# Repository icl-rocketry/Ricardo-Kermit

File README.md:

# Kermit
RAE board designed for data acquisition. All versions currently include power regulation for different types of analog sensors, as well as ADC and TC inputs.

# Supported Versions

## v3
v3 Kermit (nicknamed Kermit mini) includes:
  - [Ricardo Template](https://github.com/icl-rocketry/Ricardo-BoardTemplate) components.
  - 5V and 12V power outputs from an LDO.
  - 4 ADC channels with a theoretical maximum of 64kSPS from 1x ADS131M04 chip. All 4 channels can be configured for differential and single-ended inputs, 4-20mA input, voltage sensor input.
  - 2 Thermocouple chips (MAX31856) supporting every type of thermocouple.
  - SD Card for in-flight, and high rate, data acquisition.
  
## v2
v2 Kermit includes:
  - [Ricardo Template](https://github.com/icl-rocketry/Ricardo-BoardTemplate) components.
  - 5V and 10V power outputs from an LDO.
  - 12 ADC channels with a theoretical maximum of 32kSPS from 2x ADS131M06 chips. All 12 channels can be configured for differential and single-ended inputs, and 3.3V supply voltage sensors. 10 of the channels can be configured for 5v voltage-based sensors, and 2 of the channels can be configured for 4-20mA sensors (10V supply).
  - 4 Thermocouple chips (MAX31856) supporting every type of thermocouple.
  - SD Card for in-flight, and high rate, data acquisition.

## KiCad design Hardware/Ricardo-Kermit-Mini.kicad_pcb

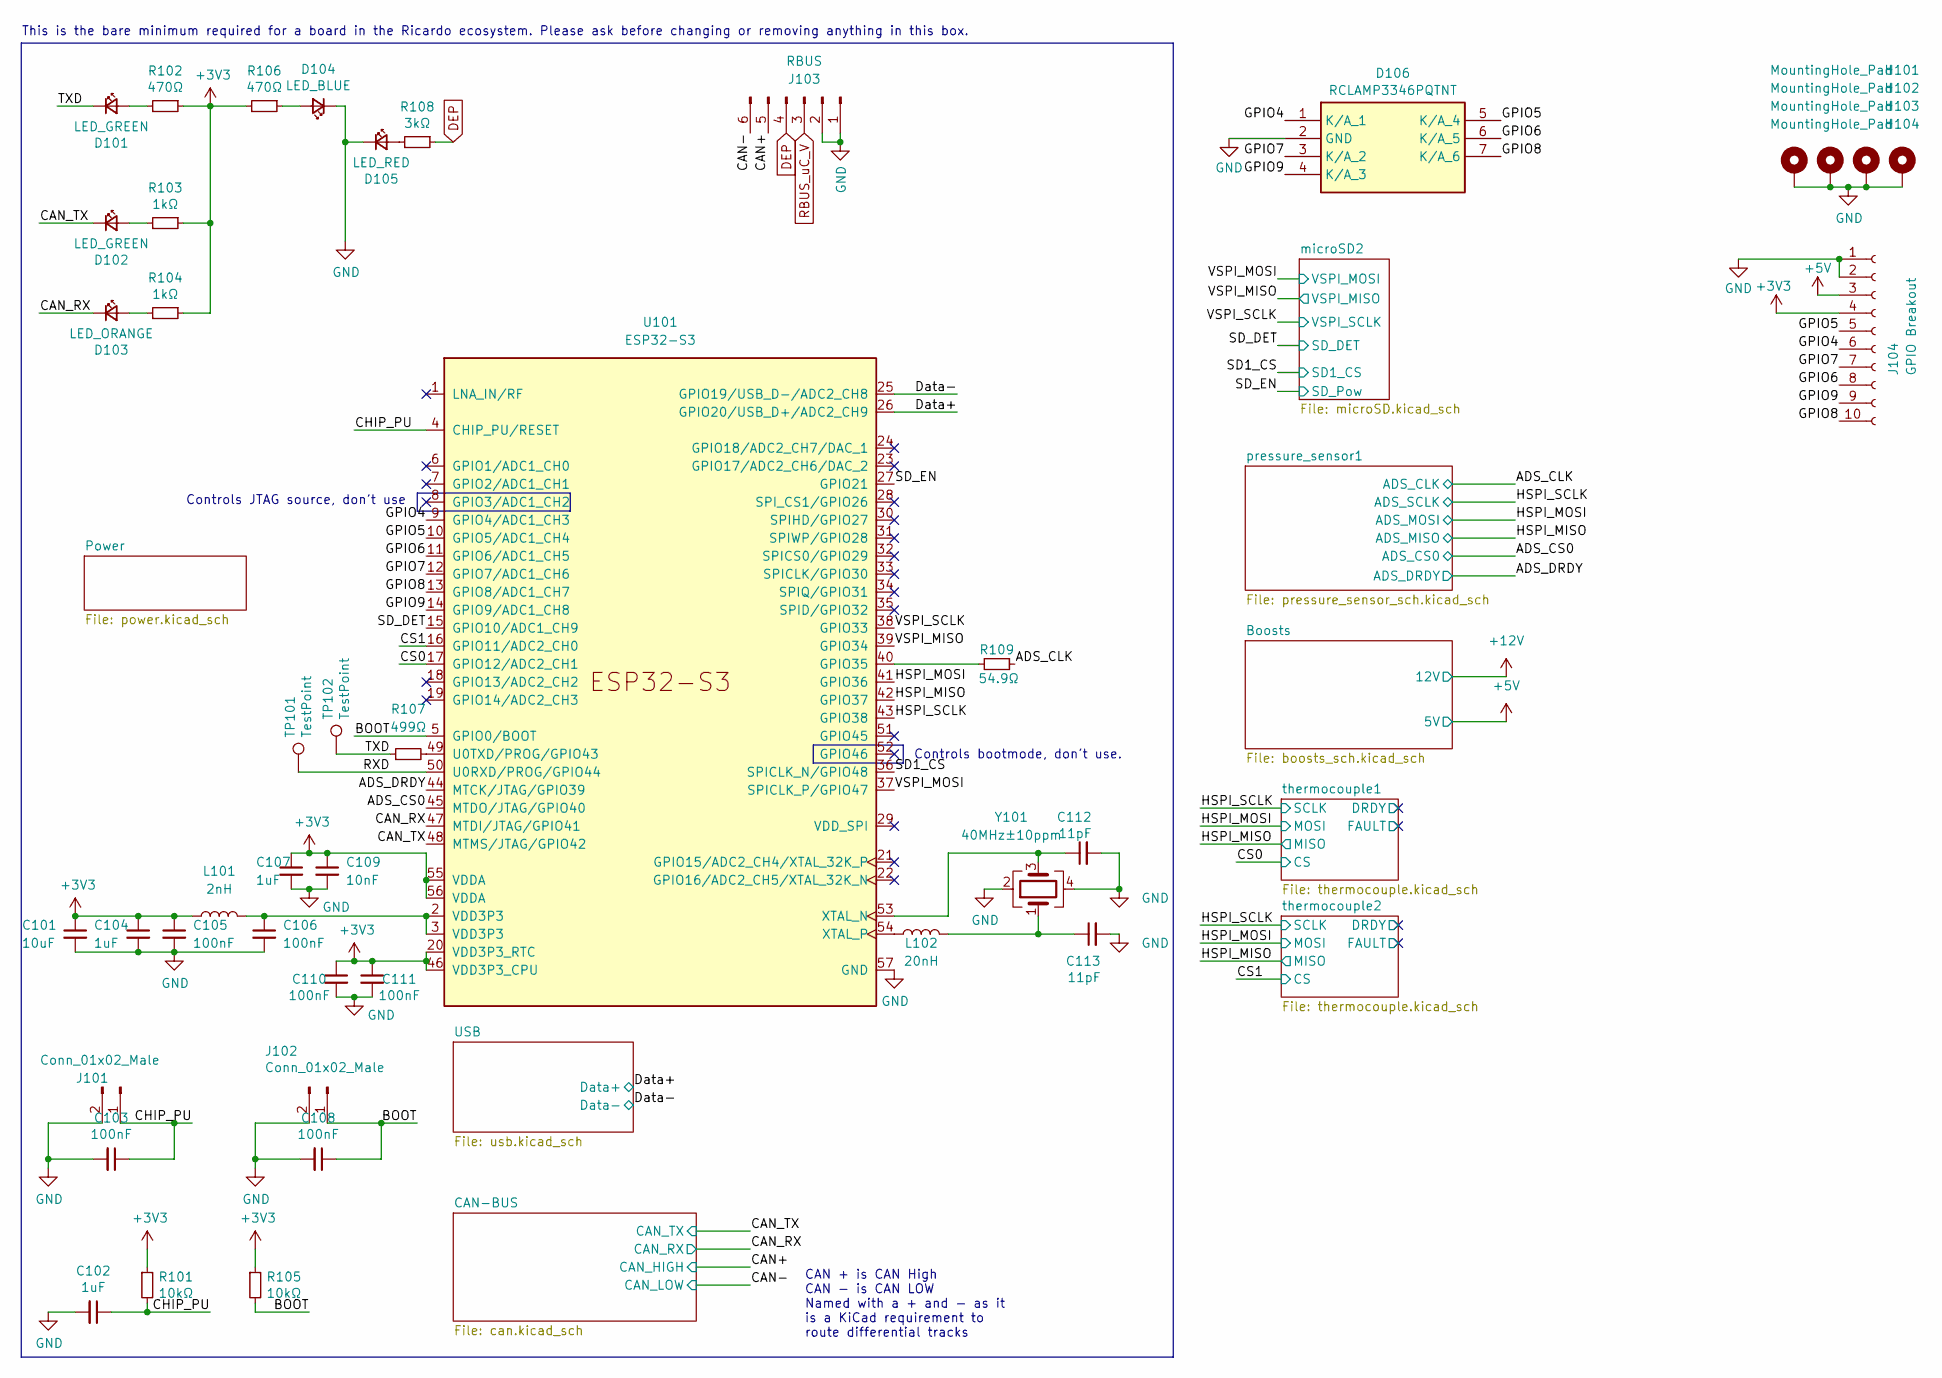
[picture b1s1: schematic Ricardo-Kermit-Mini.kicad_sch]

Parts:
C101: 10uF; C_0402_1005Metric
C102, C104, C107: 1uF; C_0402_1005Metric
C103, C105, C106, C108, C110, C111: 100nF; C_0402_1005Metric
C109: 10nF; C_0402_1005Metric
C112, C113: 11pF; C_0402_1005Metric
D101, D102: LED_GREEN; LED_0402_1005Metric
D103: LED_ORANGE; LED_0402_1005Metric
D104: LED_BLUE; LED_0402_1005Metric
D105: LED_RED; LED_0402_1005Metric
D106: RCLAMP3346PQTNT; Mouser Part Number 947-RCLAMP3346PQTNT
H101, H102, H103, H104: MountingHole_Pad; MountingHole_3.2mm_M3_DIN965_Pad
J101, J102: Conn_01x02_Male; PinHeader_1x02_P2.54mm_Vertical
J103: RBUS; Molex_Mini-Fit_Jr_5566-06A_2x03_P4.20mm_Vertical
J104: GPIO Breakout; PinSocket_2x05_P2.54mm_Vertical
L101: 2nH; L_0402_1005Metric
L102: 20nH; L_0402_1005Metric
R101, R105: 10kΩ; R_0402_1005Metric
R102, R106: 470Ω; R_0402_1005Metric
R103, R104: 1kΩ; R_0402_1005Metric
R107: 499Ω; R_0402_1005Metric; MPN AC0402FR-07499RL
R108: 3kΩ; R_0402_1005Metric
R109: 54.9Ω; R_0402_1005Metric
TP101, TP102: TestPoint; TestPoint_Pad_D1.0mm
U101: ESP32-S3; QFN40P700X700X90-57N
Y101: 40MHz±10ppm; Crystal_SMD_2016-4Pin_2.0x1.6mm; MPN R940000171

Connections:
+3V3: C101.1, C104.1, C105.1, C107.1, C109.1, C110.1, C111.1, J104.4, L101.1, R101.1, R102.1, R103.1, R104.1, R105.1, R106.2, U101.20 (VDD3P3_RTC), U101.46 (VDD3P3_CPU), U101.55 (VDDA), U101.56 (VDDA); also elsewhere on the board
+5V: J104.3; also elsewhere on the board
/ADS_CLK: R109.1; also elsewhere on the board
/ADS_CS0: U101.45 (MTDO/JTAG/GPIO40); also elsewhere on the board
/ADS_DRDY: U101.44 (MTCK/JTAG/GPIO39); also elsewhere on the board
/BOOT: C108.1, J102.1, R105.2, U101.5 (GPIO0/BOOT)
/CAN+: J103.5; also elsewhere on the board
/CAN-: J103.6; also elsewhere on the board
/CAN_RX: D103.1 (K), U101.47 (MTDI/JTAG/GPIO41); also elsewhere on the board
/CAN_TX: D102.1 (K), U101.48 (MTMS/JTAG/GPIO42); also elsewhere on the board
/CHIP_PU: C102.1, C103.1, J101.1, R101.2, U101.4 (CHIP_PU/RESET)
/CS0: U101.17 (GPIO12/ADC2_CH1); also elsewhere on the board
/CS1: U101.16 (GPIO11/ADC2_CH0); also elsewhere on the board
/Data+: U101.26 (GPIO20/USB_D+/ADC2_CH9); also elsewhere on the board
/Data-: U101.25 (GPIO19/USB_D-/ADC2_CH8); also elsewhere on the board
/GPIO4: D106.1 (K/A_1), J104.6, U101.9 (GPIO4/ADC1_CH3)
/GPIO5: D106.5 (K/A_4), J104.5, U101.10 (GPIO5/ADC1_CH4)
/GPIO6: D106.6 (K/A_5), J104.8, U101.11 (GPIO6/ADC1_CH5)
/GPIO7: D106.3 (K/A_2), J104.7, U101.12 (GPIO7/ADC1_CH6)
/GPIO8: D106.7 (K/A_6), J104.10, U101.13 (GPIO8/ADC1_CH7)
/GPIO9: D106.4 (K/A_3), J104.9, U101.14 (GPIO9/ADC1_CH8)
/HSPI_MISO: U101.42 (GPIO37); also elsewhere on the board
/HSPI_MOSI: U101.41 (GPIO36); also elsewhere on the board
/HSPI_SCLK: U101.43 (GPIO38); also elsewhere on the board
/RXD: TP101.1, U101.50 (U0RXD/PROG/GPIO44)
/SD1_CS: U101.36 (SPICLK_N/GPIO48); also elsewhere on the board
/SD_DET: U101.15 (GPIO10/ADC1_CH9); also elsewhere on the board
/SD_EN: U101.27 (GPIO21); also elsewhere on the board
/TXD: D101.1 (K), R107.1, TP102.1
/VSPI_MISO: U101.39 (GPIO34); also elsewhere on the board
/VSPI_MOSI: U101.37 (SPICLK_P/GPIO47); also elsewhere on the board
/VSPI_SCLK: U101.38 (GPIO33); also elsewhere on the board
DEP: J103.4, R108.1
GND: C101.2, C102.2, C103.2, C104.2, C105.2, C106.2, C107.2, C108.2, C109.2, C110.2, C111.2, C112.2, C113.2, D104.1 (K), D105.1 (K), D106.2 (GND), H101.1, H102.1, H103.1, H104.1, J101.2, J102.2, J103.1, J103.2, J104.1, J104.2, U101.57 (GND), Y101.2, Y101.4; also elsewhere on the board
unnamed: C106.1, L101.2, U101.2 (VDD3P3), U101.3 (VDD3P3)
unnamed: C113.1, L102.2, Y101.1
unnamed: D101.2 (A), R102.2
unnamed: D102.2 (A), R103.2
unnamed: D103.2 (A), R104.2
unnamed: D104.2 (A), R106.1
unnamed: D105.2 (A), R108.2
unnamed: R109.2, U101.40 (GPIO35)
unnamed: R107.2, U101.49 (U0TXD/PROG/GPIO43)
unnamed: C112.1, U101.53 (XTAL_N), Y101.3
unnamed: L102.1, U101.54 (XTAL_P)
RBUS_uC_V: J103.3; also elsewhere on the board

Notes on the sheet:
Controls bootmode, don't use.
This is the bare minimum required for a board in the Ricardo ecosystem. Please ask before changing or removing anything in this box.
CAN + is CAN High CAN - is CAN LOW Named with a + and - as it is a KiCad requirement to route differential tracks
Controls JTAG source, don't use

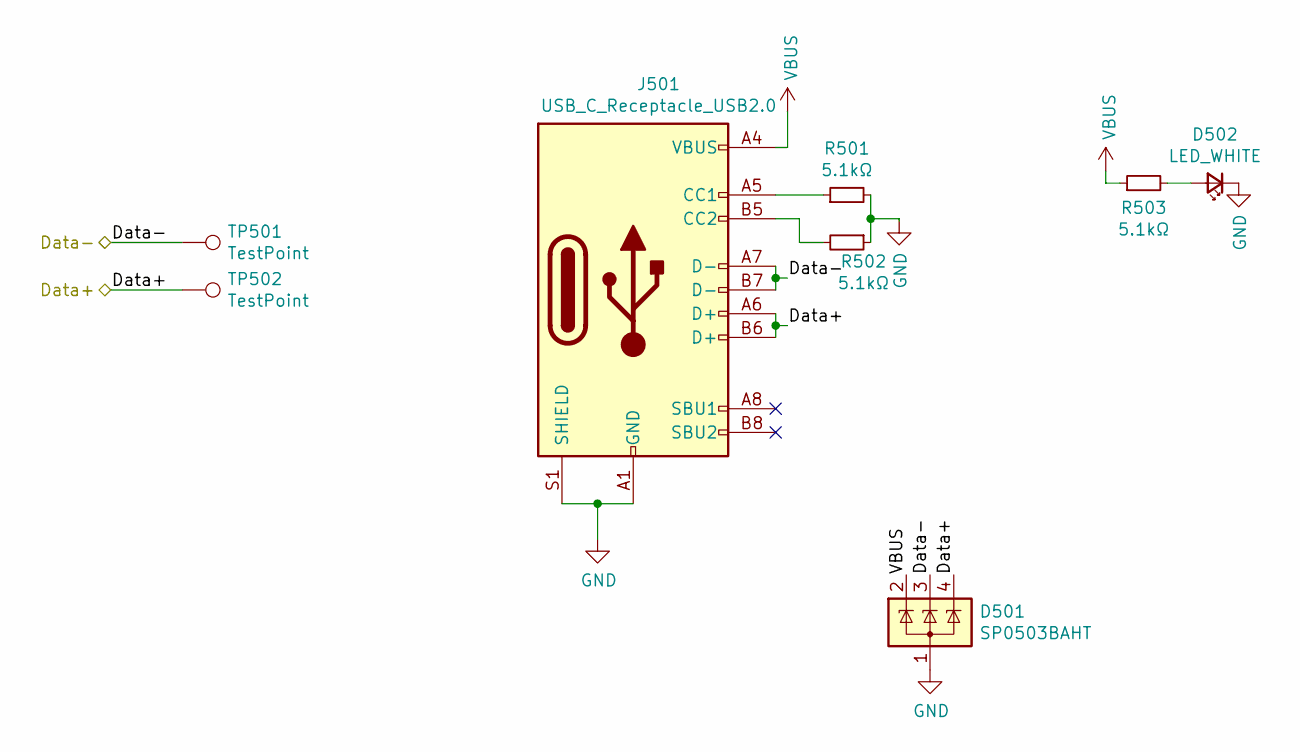
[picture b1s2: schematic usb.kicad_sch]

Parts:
D501: SP0503BAHT; SOT-143
D502: LED_WHITE; LED_0402_1005Metric
J501: USB_C_Receptacle_USB2.0; USB_C_Receptacle_Palconn_UTC16-G
R501, R502, R503: 5.1kΩ; R_0402_1005Metric
TP501, TP502: TestPoint; TestPoint_Pad_D1.0mm

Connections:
/Data+: D501.4 (K), J501.A6 (D+), J501.B6 (D+), TP502.1; also elsewhere on the board
/Data-: D501.3 (K), J501.A7 (D-), J501.B7 (D-), TP501.1; also elsewhere on the board
GND: D501.1 (A), D502.1 (K), J501.A1 (GND), J501.A12 (GND), J501.B1 (GND), J501.B12 (GND), J501.S1 (SHIELD), R501.2, R502.1; also elsewhere on the board
unnamed: D502.2 (A), R503.2
unnamed: J501.A5 (CC1), R501.1
unnamed: J501.B5 (CC2), R502.2
VBUS: D501.2 (K), J501.A4 (VBUS), J501.A9 (VBUS), J501.B4 (VBUS), J501.B9 (VBUS), R503.1; also elsewhere on the board

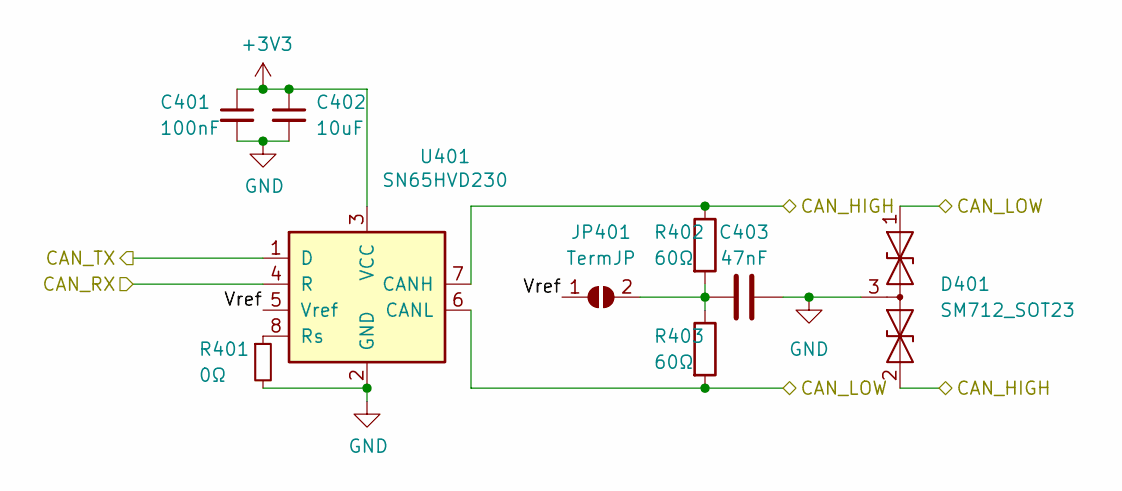
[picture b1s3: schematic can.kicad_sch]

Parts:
C401: 100nF; C_0402_1005Metric
C402: 10uF; C_0402_1005Metric
C403: 47nF; C_0402_1005Metric
D401: SM712_SOT23; SOT-23
JP401: TermJP; SolderJumper-2_P1.3mm_Open_RoundedPad1.0x1.5mm
R401: 0Ω; R_0603_1608Metric
R402, R403: 60Ω; R_0603_1608Metric
U401: SN65HVD230; SOIC-8_3.9x4.9mm_P1.27mm

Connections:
+3V3: C401.1, C402.1, U401.3 (VCC); also elsewhere on the board
/CAN+: D401.2 (A2), R402.1, U401.7 (CANH); also elsewhere on the board
/CAN-: D401.1 (A1), R403.2, U401.6 (CANL); also elsewhere on the board
/CAN-BUS/Vref: JP401.1 (A), U401.5 (Vref)
/CAN_RX: U401.4 (R); also elsewhere on the board
/CAN_TX: U401.1 (D); also elsewhere on the board
GND: C401.2, C402.2, C403.2, D401.3 (common), R401.2, U401.2 (GND); also elsewhere on the board
unnamed: C403.1, JP401.2 (B), R402.2, R403.1
unnamed: R401.1, U401.8 (Rs)

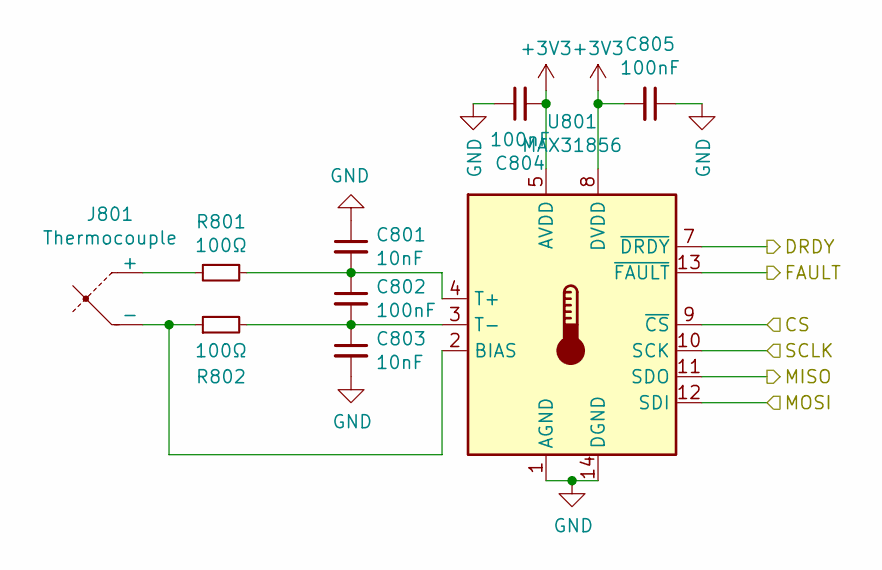
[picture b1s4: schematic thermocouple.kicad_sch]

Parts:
C801, C803: 10nF; C_0402_1005Metric
C802, C804, C805: 100nF; C_0402_1005Metric
J801: Thermocouple; Molex_Nano-Fit_105313-xx02_1x02_P2.50mm_Horizontal
R801, R802: 100Ω; R_0402_1005Metric
U801: MAX31856; TSSOP-14_4.4x5mm_P0.65mm

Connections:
+3V3: C804.2, C805.2, U801.5 (AVDD), U801.8 (DVDD); also elsewhere on the board
/CS0: U801.9 (~CS); also elsewhere on the board
/HSPI_MISO: U801.11 (SDO); also elsewhere on the board
/HSPI_MOSI: U801.12 (SDI); also elsewhere on the board
/HSPI_SCLK: U801.10 (SCK); also elsewhere on the board
/thermocouple1/DRDY: U801.7 (~DRDY)
/thermocouple1/FAULT: U801.13 (~FAULT)
GND: C801.1, C803.2, C804.1, C805.1, U801.1 (AGND), U801.14 (DGND); also elsewhere on the board
unnamed: J801.1 (+), R801.2
unnamed: J801.2 (-), R802.1, U801.2 (BIAS)
unnamed: C801.2, C802.1, R801.1, U801.4 (T+)
unnamed: C802.2, C803.1, R802.2, U801.3 (T-)

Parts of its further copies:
C901, C903: 10nF; C_0402_1005Metric
C902, C904, C905: 100nF; C_0402_1005Metric
J901: Thermocouple; Molex_Nano-Fit_105313-xx02_1x02_P2.50mm_Horizontal
R901, R902: 100Ω; R_0402_1005Metric
U901: MAX31856; TSSOP-14_4.4x5mm_P0.65mm

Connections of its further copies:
+3V3: C904.2, C905.2, U901.5 (AVDD), U901.8 (DVDD); also elsewhere on the board
/CS1: U901.9 (~CS); also elsewhere on the board
/HSPI_MISO: U901.11 (SDO); also elsewhere on the board
/HSPI_MOSI: U901.12 (SDI); also elsewhere on the board
/HSPI_SCLK: U901.10 (SCK); also elsewhere on the board
/thermocouple2/DRDY: U901.7 (~DRDY)
/thermocouple2/FAULT: U901.13 (~FAULT)
GND: C901.1, C903.2, C904.1, C905.1, U901.1 (AGND), U901.14 (DGND); also elsewhere on the board
unnamed: J901.1 (+), R901.2
unnamed: J901.2 (-), R902.1, U901.2 (BIAS)
unnamed: C901.2, C902.1, R901.1, U901.4 (T+)
unnamed: C902.2, C903.1, R902.2, U901.3 (T-)

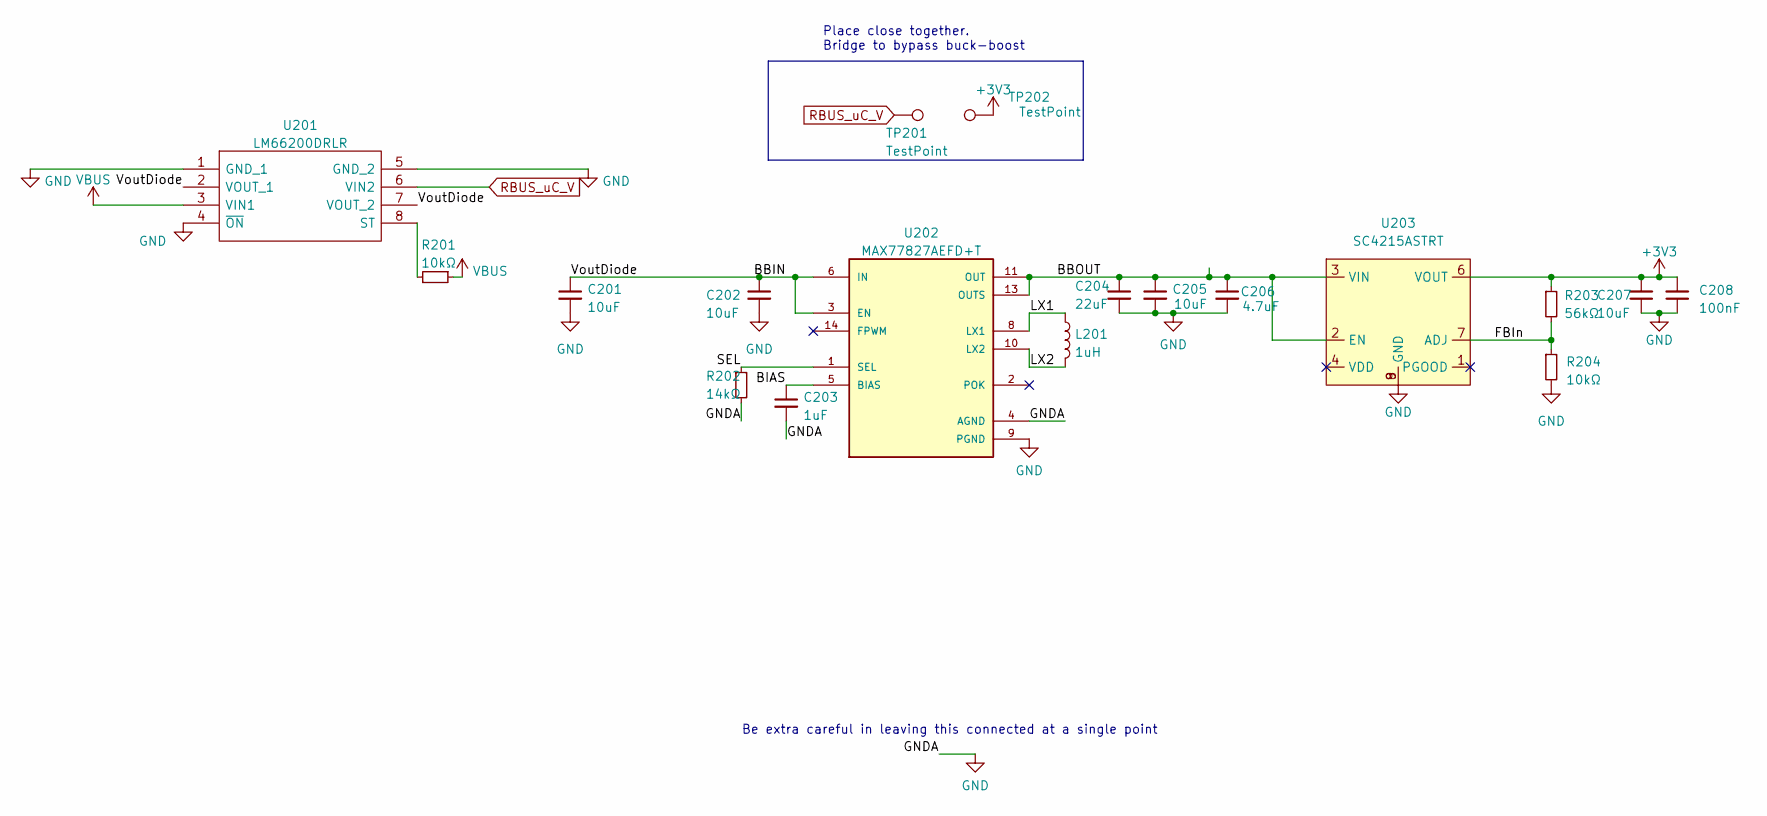
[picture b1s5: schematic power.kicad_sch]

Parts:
C201, C205, C207: 10uF; C_0402_1005Metric
C202: 10uF; C_0603_1608Metric
C203: 1uF; C_0402_1005Metric
C204: 22uF; C_0603_1608Metric
C206: 4.7uF; C_0402_1005Metric
C208: 100nF; C_0402_1005Metric
L201: 1uH; L_0805_2012Metric
R201, R204: 10kΩ; R_0402_1005Metric
R202: 14kΩ; R_0402_1005Metric
R203: 56kΩ; R_0402_1005Metric
TP201, TP202: TestPoint; TestPoint_Pad_D1.5mm
U201: LM66200DRLR; SOTFL50P160X60-8N; Manufacturer_Part_Number LM66200DRLR; Mouser Part Number 595-LM66200DRLR
U202: MAX77827AEFD+T; CONV_MAX77827AEFD+T; PARTREV B
U203: SC4215ASTRT; SOIC127P599X175-9N

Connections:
+3V3: C207.2, C208.2, R203.1, TP202.1, U203.6 (VOUT); also elsewhere on the board
/Power/BBIN: C201.1, C202.1, U201.2 (VOUT_1), U201.7 (VOUT_2), U202.3 (EN), U202.6 (IN)
/Power/BBOUT: C204.1, C205.1, C206.1, U202.11 (OUT), U202.13 (OUTS), U203.2 (EN), U203.3 (VIN)
/Power/BIAS: C203.1, U202.5 (BIAS)
/Power/FBIn: R203.2, R204.1, U203.7 (ADJ)
/Power/LX1: L201.1, U202.8 (LX1)
/Power/LX2: L201.2, U202.10 (LX2)
/Power/SEL: R202.1, U202.1 (SEL)
GND: C201.2, C202.2, C203.2, C204.2, C205.2, C206.2, C207.1, C208.1, R202.2, R204.2, U201.1 (GND_1), U201.4 (~ON), U201.5 (GND_2), U202.4 (AGND), U202.9 (PGND), U203.8 (GND), U203.9 (GND); also elsewhere on the board
unnamed: R201.2, U201.8 (ST)
RBUS_uC_V: TP201.1, U201.6 (VIN2); also elsewhere on the board
VBUS: R201.1, U201.3 (VIN1); also elsewhere on the board

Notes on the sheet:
Place close together. Bridge to bypass buck-boost
Be extra careful in leaving this connected at a single point

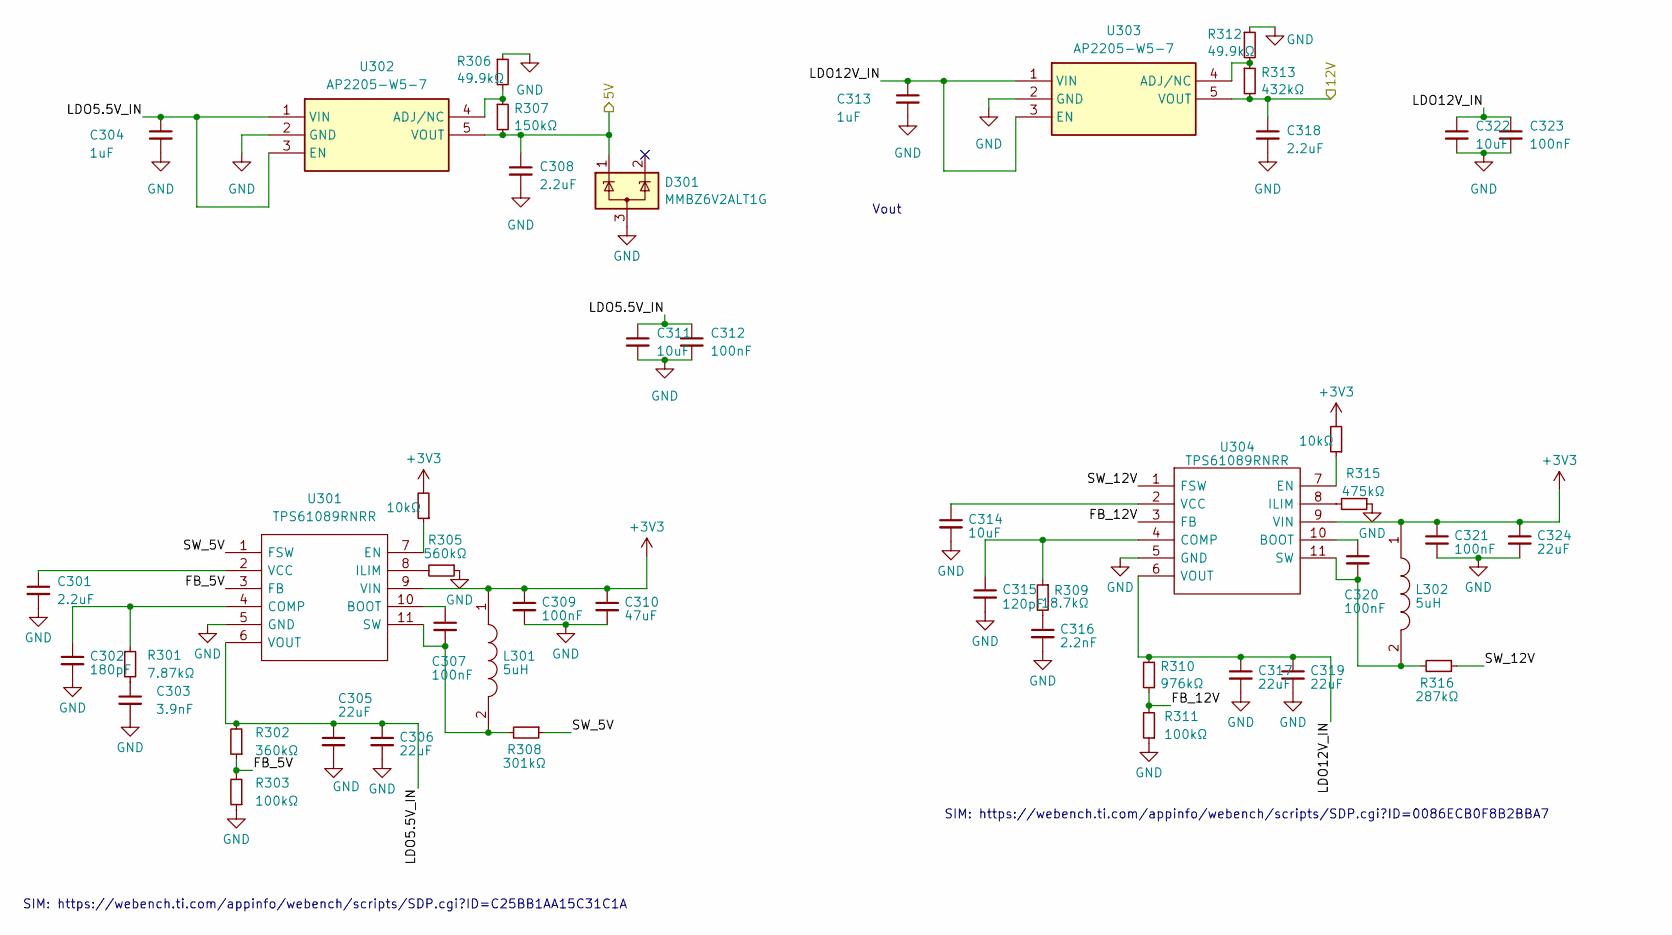
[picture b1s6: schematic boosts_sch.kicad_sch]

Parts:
C301: 2.2uF; C_0603_1608Metric
C302: 180pF; C_0402_1005Metric
C303: 3.9nF; C_0402_1005Metric
C304, C313: 1uF; C_0402_1005Metric; MPN CL05X105KA5NQNC
C305, C306, C317, C319: 22uF; C_0805_2012Metric
C307, C309, C320, C321: 100nF; C_0402_1005Metric
C308, C318: 2.2uF; C_0402_1005Metric; MPN GRM155R61E225ME15D
C310: 47uF; C_1206_3216Metric
C311: 10uF; C_0402_1005Metric; MPN CL05A106MP8NUB8
C312, C323: 100nF; C_0402_1005Metric; MPN C1005X5R1E104KT000E
C314: 10uF; C_0603_1608Metric
C315: 120pF; C_0402_1005Metric
C316: 2.2nF; C_0402_1005Metric
C322: 10uF; C_0603_1608Metric; MPN TMK107BBJ106MA-T
C324: 22uF; C_1206_3216Metric
D301: MMBZ6V2ALT1G; SOT-23; MPN MMBZ6V2ALT1G
L301, L302: 5uH; IND_SRP6540-390M; Manufacturer_Part_Number SRR6038-5R0Y; Mouser Part Number 652-SRR6038-5R0Y
R301: 7.87kΩ; R_0402_1005Metric
R302: 360kΩ; R_0402_1005Metric
R303, R311: 100kΩ; R_0402_1005Metric
R304, R314: 10kΩ; R_0402_1005Metric
R305: 560kΩ; R_0402_1005Metric
R306, R312: 49.9kΩ; R_0402_1005Metric
R307: 150kΩ; R_0402_1005Metric
R308: 301kΩ; R_0402_1005Metric
R309: 18.7kΩ; R_0402_1005Metric
R310: 976kΩ; R_0402_1005Metric
R313: 432kΩ; R_0402_1005Metric
R315: 475kΩ; R_0402_1005Metric
R316: 287kΩ; R_0402_1005Metric
U301, U304: TPS61089RNRR; IC_TPS61089RNRR; Manufacturer_Part_Number TPS61089RNRR; Mouser Part Number 595-TPS61089RNRR
U302, U303: AP2205-W5-7; SOT95P282X145-5N; Mouser Part Number 621-AP2205-W5-7

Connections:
+3V3: C309.1, C310.1, C321.1, C324.1, L301.1, L302.1, R304.2, R314.2, U301.9 (VIN), U304.9 (VIN); also elsewhere on the board
+5V: C308.1, D301.1 (K), R307.2, U302.5 (VOUT); also elsewhere on the board
+12V: C318.1, R313.2, U303.5 (VOUT); also elsewhere on the board
/Boosts/FB_5V: R302.1, R303.2, U301.3 (FB)
/Boosts/FB_12V: R310.1, R311.2, U304.3 (FB)
/Boosts/LDO5.5V_IN: C304.1, C305.1, C306.1, C311.1, C312.1, R302.2, U301.6 (VOUT), U302.1 (VIN), U302.3 (EN)
/Boosts/LDO12V_IN: C313.1, C317.1, C319.1, C322.1, C323.1, R310.2, U303.1 (VIN), U303.3 (EN), U304.6 (VOUT)
/Boosts/SW_5V: R308.1, U301.1 (FSW)
/Boosts/SW_12V: R316.1, U304.1 (FSW)
GND: C301.2, C302.2, C303.2, C304.2, C305.2, C306.2, C308.2, C309.2, C310.2, C311.2, C312.2, C313.2, C314.2, C315.2, C316.2, C317.2, C318.2, C319.2, C321.2, C322.2, C323.2, C324.2, D301.3 (A), R303.1, R305.1, R306.1, R311.1, R312.1, R315.1, U301.5 (GND), U302.2 (GND), U303.2 (GND), U304.5 (GND); also elsewhere on the board
unnamed: C303.1, R301.2
unnamed: C316.1, R309.2
unnamed: C307.1, U301.10 (BOOT)
unnamed: C302.1, R301.1, U301.4 (COMP)
unnamed: R304.1, U301.7 (EN)
unnamed: R305.2, U301.8 (ILIM)
unnamed: C307.2, L301.2, R308.2, U301.11 (SW)
unnamed: C301.1, U301.2 (VCC)
unnamed: R306.2, R307.1, U302.4 (ADJ/NC)
unnamed: R312.2, R313.1, U303.4 (ADJ/NC)
unnamed: C320.1, U304.10 (BOOT)
unnamed: C315.1, R309.1, U304.4 (COMP)
unnamed: R314.1, U304.7 (EN)
unnamed: R315.2, U304.8 (ILIM)
unnamed: C320.2, L302.2, R316.2, U304.11 (SW)
unnamed: C314.1, U304.2 (VCC)

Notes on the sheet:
SIM: https://webench.ti.com/appinfo/webench/scripts/SDP.cgi?ID=C25BB1AA15C31C1A
Vout
SIM: https://webench.ti.com/appinfo/webench/scripts/SDP.cgi?ID=0086ECB0F8B2BBA7

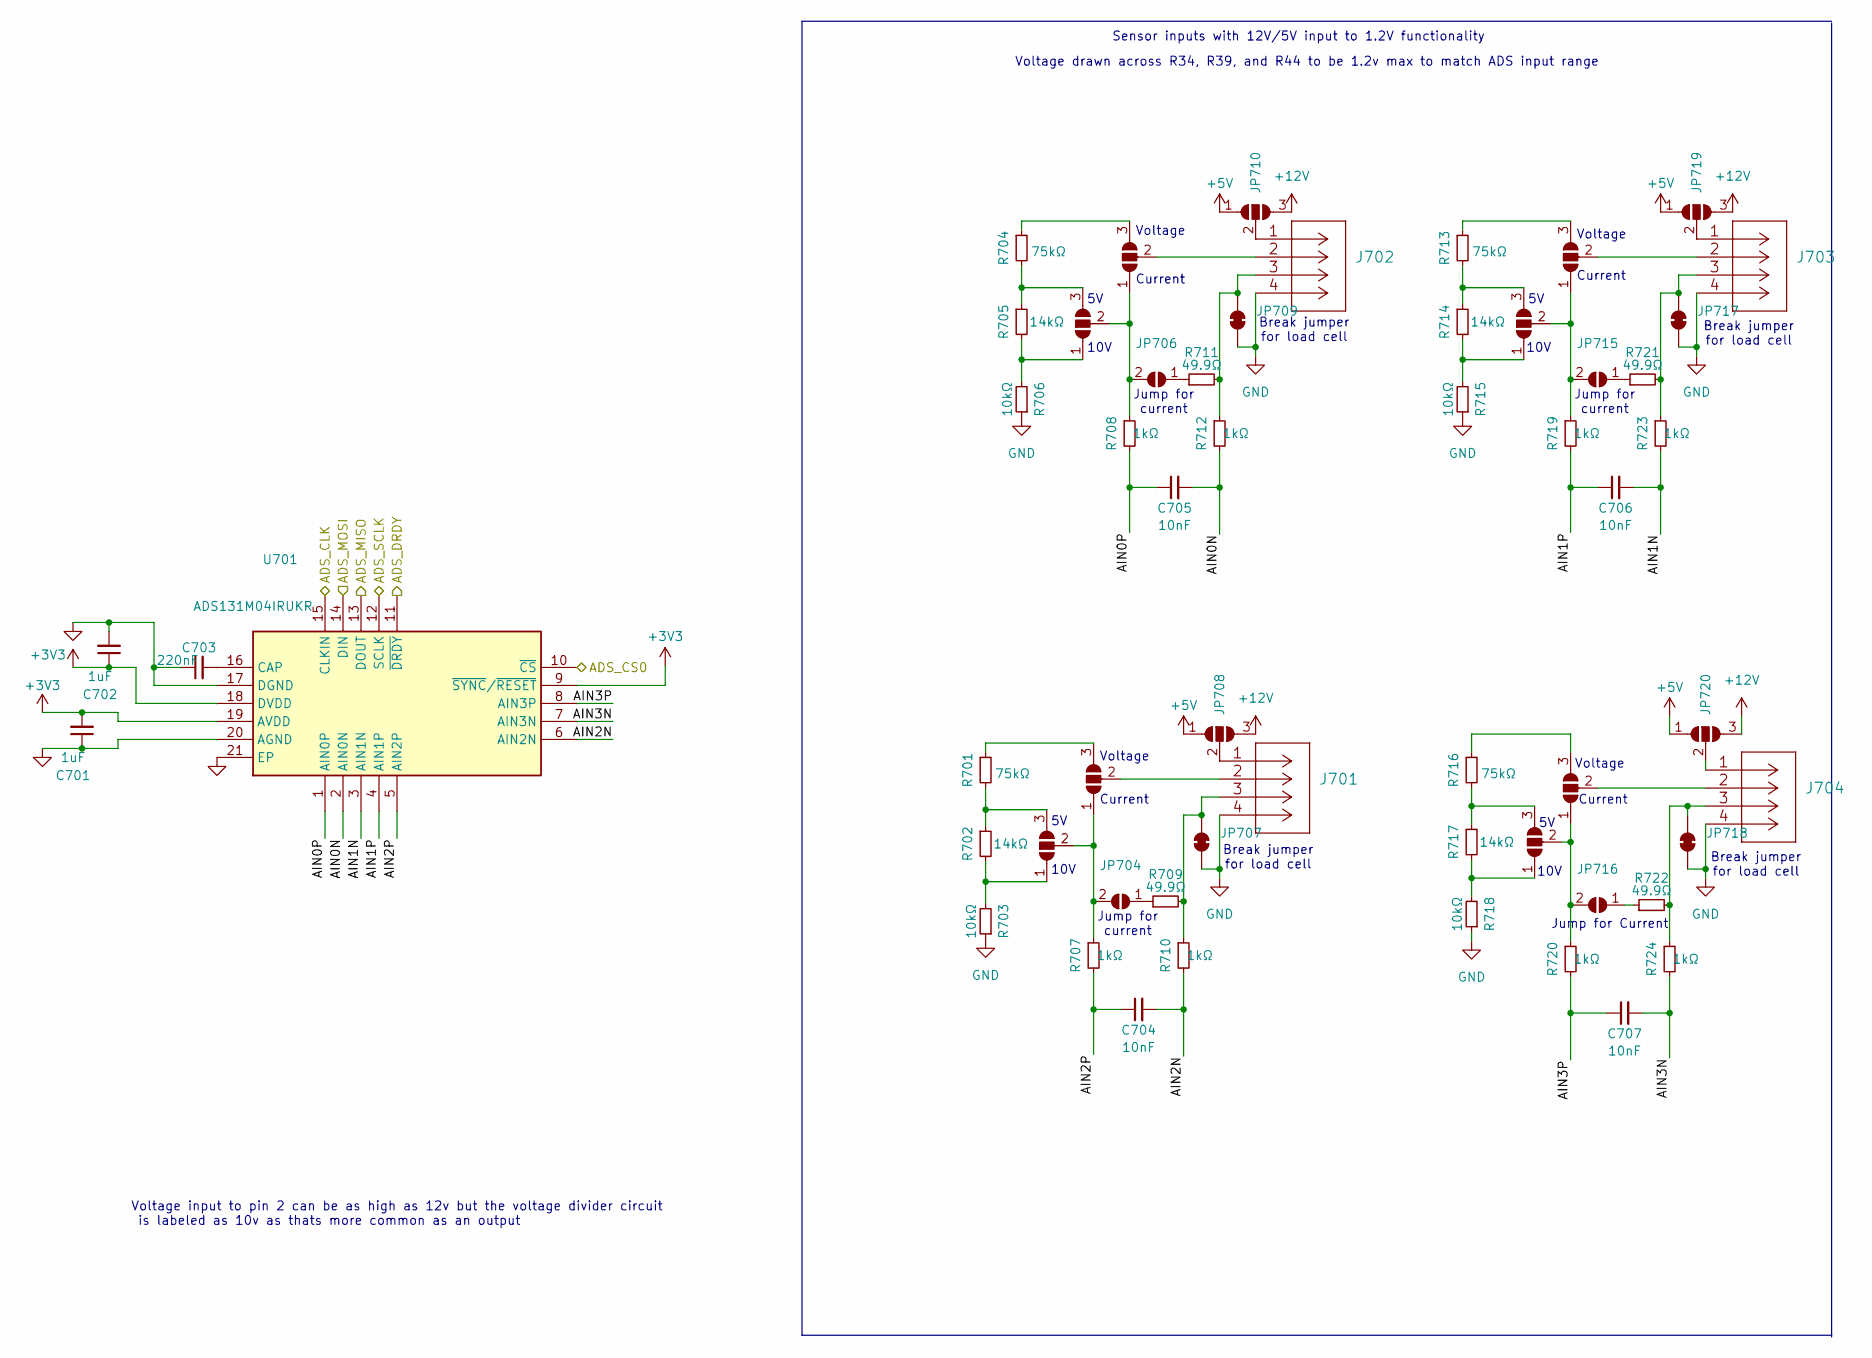
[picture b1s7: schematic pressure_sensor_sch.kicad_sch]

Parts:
C701, C702: 1uF; C_0402_1005Metric
C703: 220nF; C_0402_1005Metric
C704, C705, C706, C707: 10nF; C_0402_1005Metric
J701, J702, J703, J704: 1053131104; Molex_Nano-Fit_105313-xx04_1x04_P2.50mm_Horizontal
JP701, JP702, JP703, JP705, JP708, JP710, JP711, JP712, JP713, JP714, JP719, JP720: SolderJumper_3_Open; SolderJumper-3_P1.3mm_Open_RoundedPad1.0x1.5mm_NumberLabels
JP704, JP706, JP715, JP716: SolderJumper_2_Open; small_2_pad_jumper_open
JP707, JP709, JP717, JP718: SolderJumper_2_Bridged; small_2_pad_jumper_closed
R701, R713, R716: 75kΩ; R_0402_1005Metric
R702, R714, R717: 14kΩ; R_0402_1005Metric
R703, R715, R718: 10kΩ; R_0402_1005Metric
R704: 75kΩ; R_0402_1005Metric; MPN RT0402BRD0775KL
R705: 14kΩ; R_0402_1005Metric; MPN 0402WGF1402TCE
R706: 10kΩ; R_0402_1005Metric; MPN ERA2ARB103X
R707, R708, R710, R712, R719, R720, R723, R724: 1kΩ; R_0402_1005Metric
R709, R711, R721, R722: 49.9Ω; R_0402_1005Metric; MPN RT0402BRD0749R9L
U701: ADS131M04IRUKR; QFN40P300X300X80-21N-D; Manufacturer_Part_Number ADS131M04IRUKR; Mouser Part Number 595-ADS131M04IRUKR

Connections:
+3V3: C701.2, C702.1, U701.9 (~SYNC/~RESET), U701.18 (DVDD), U701.19 (AVDD); also elsewhere on the board
+5V: JP708.1 (A), JP710.1 (A), JP719.1 (A), JP720.1 (A); also elsewhere on the board
+12V: JP708.3 (B), JP710.3 (B), JP719.3 (B), JP720.3 (B); also elsewhere on the board
/ADS_CLK: U701.15 (CLKIN); also elsewhere on the board
/ADS_CS0: U701.10 (~CS); also elsewhere on the board
/ADS_DRDY: U701.11 (~DRDY); also elsewhere on the board
/HSPI_MISO: U701.13 (DOUT); also elsewhere on the board
/HSPI_MOSI: U701.14 (DIN); also elsewhere on the board
/HSPI_SCLK: U701.12 (SCLK); also elsewhere on the board
/pressure_sensor1/AIN0N: C705.2, R712.2, U701.2 (AIN0N)
/pressure_sensor1/AIN0P: C705.1, R708.2, U701.1 (AIN0P)
/pressure_sensor1/AIN1N: C706.2, R723.2, U701.3 (AIN1N)
/pressure_sensor1/AIN1P: C706.1, R719.2, U701.4 (AIN1P)
/pressure_sensor1/AIN2N: C704.2, R710.2, U701.6 (AIN2N)
/pressure_sensor1/AIN2P: C704.1, R707.2, U701.5 (AIN2P)
/pressure_sensor1/AIN3N: C707.2, R724.2, U701.7 (AIN3N)
/pressure_sensor1/AIN3P: C707.1, R720.2, U701.8 (AIN3P)
GND: C701.1, C702.2, C703.1, J701.4, J702.4, J703.4, J704.4, JP707.1 (A), JP709.1 (A), JP717.1 (A), JP718.1 (A), R703.1, R706.1, R715.1, R718.1, U701.17 (DGND), U701.20 (AGND), U701.21 (EP); also elsewhere on the board
unnamed: JP701.1 (A), R702.2, R703.2
unnamed: JP701.3 (B), R701.2, R702.1
unnamed: JP701.2 (C), JP703.1 (A), JP704.2 (B), R707.1
unnamed: JP702.1 (A), R705.2, R706.2
unnamed: JP702.3 (B), R704.2, R705.1
unnamed: JP702.2 (C), JP705.1 (A), JP706.2 (B), R708.1
unnamed: JP703.3 (B), R701.1
unnamed: J701.2, JP703.2 (C)
unnamed: JP704.1 (A), R709.1
unnamed: JP705.3 (B), R704.1
unnamed: J702.2, JP705.2 (C)
unnamed: JP706.1 (A), R711.1
unnamed: J701.3, JP707.2 (B), R709.2, R710.1
unnamed: J701.1, JP708.2 (C)
unnamed: J702.3, JP709.2 (B), R711.2, R712.1
unnamed: J702.1, JP710.2 (C)
unnamed: JP711.1 (A), R714.2, R715.2
unnamed: JP711.3 (B), R713.2, R714.1
unnamed: JP711.2 (C), JP713.1 (A), JP715.2 (B), R719.1
unnamed: JP712.1 (A), R717.2, R718.2
unnamed: JP712.3 (B), R716.2, R717.1
unnamed: JP712.2 (C), JP714.1 (A), JP716.2 (B), R720.1
unnamed: JP713.3 (B), R713.1
unnamed: J703.2, JP713.2 (C)
unnamed: JP714.3 (B), R716.1
unnamed: J704.2, JP714.2 (C)
unnamed: JP715.1 (A), R721.1
unnamed: JP716.1 (A), R722.1
unnamed: J703.3, JP717.2 (B), R721.2, R723.1
unnamed: J704.3, JP718.2 (B), R722.2, R724.1
unnamed: J703.1, JP719.2 (C)
unnamed: J704.1, JP720.2 (C)
unnamed: C703.2, U701.16 (CAP)

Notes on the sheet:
Break jumper for load cell
10V
Voltage drawn across R34, R39, and R44 to be 1.2v max to match ADS input range
Jump for current
Voltage
Current
Jump for Current
Sensor inputs with 12V/5V input to 1.2V functionality
Voltage input to pin 2 can be as high as 12v but the voltage divider circuit is labeled as 10v as thats more common as an output

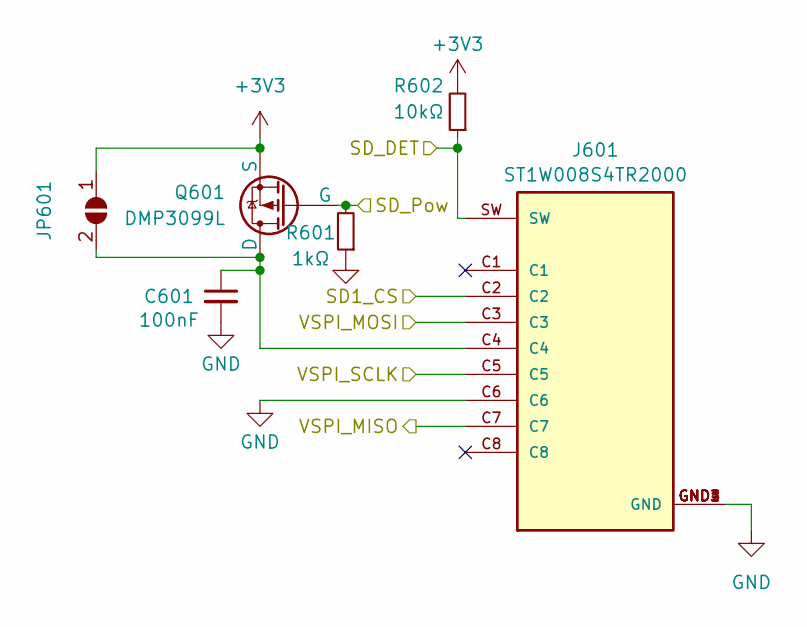
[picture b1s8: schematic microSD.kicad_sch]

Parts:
C601: 100nF; C_0402_1005Metric
J601: ST1W008S4TR2000; JAE_ST1W008S4TR2000; PARTREV 1
JP601: SolderJumper_2_Open; SmallerSolderJP
Q601: DMP3099L; SOT-23; MPN DMP3099L
R601: 1kΩ; R_0402_1005Metric
R602: 10kΩ; R_0402_1005Metric

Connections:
+3V3: JP601.1 (A), Q601.3 (S), R602.2; also elsewhere on the board
/SD1_CS: J601.C2; also elsewhere on the board
/SD_DET: J601.SW, R602.1; also elsewhere on the board
/SD_EN: Q601.2 (G), R601.2; also elsewhere on the board
/VSPI_MISO: J601.C7; also elsewhere on the board
/VSPI_MOSI: J601.C3; also elsewhere on the board
/VSPI_SCLK: J601.C5; also elsewhere on the board
GND: C601.2, J601.C6, J601.GND1 (GND), J601.GND2 (GND), J601.GND3 (GND), J601.GND4 (GND), R601.1; also elsewhere on the board
unnamed: C601.1, J601.C4, JP601.2 (B), Q601.1 (D)

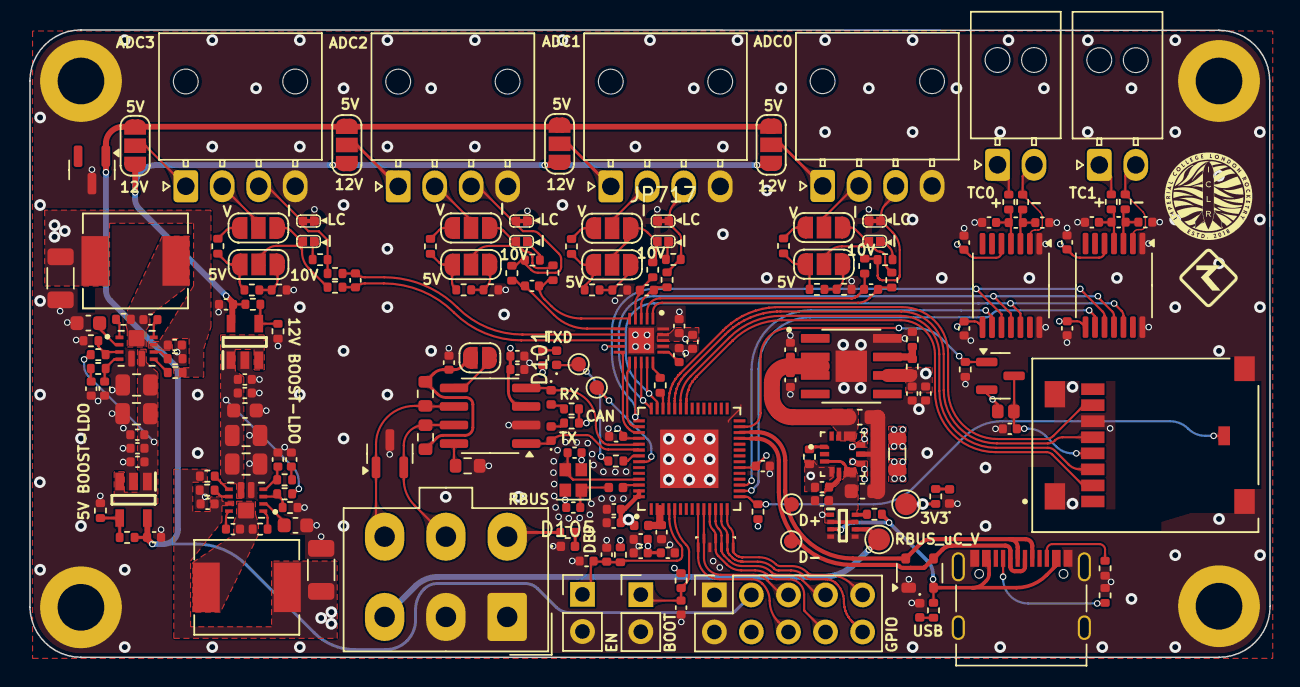
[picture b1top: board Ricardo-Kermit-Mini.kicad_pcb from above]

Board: 4 copper layers, 85.0 x 43.0 mm, 204 parts (0 on the bottom side), 134 nets.

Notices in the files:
parts and their libraries:
Copyright 2021 Accelerated Designs. All rights reserved.
